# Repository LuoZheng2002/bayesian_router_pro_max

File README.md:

# On Windows:
At the root of the repository, double click on "installer.msi" to install and run the application.
# On Other Platform:
Download Rust and Tauri development toolchain, and at the repository root, run:

cargo tauri dev

for running the development version.

Or run

cargo tauri build

for building the released version.

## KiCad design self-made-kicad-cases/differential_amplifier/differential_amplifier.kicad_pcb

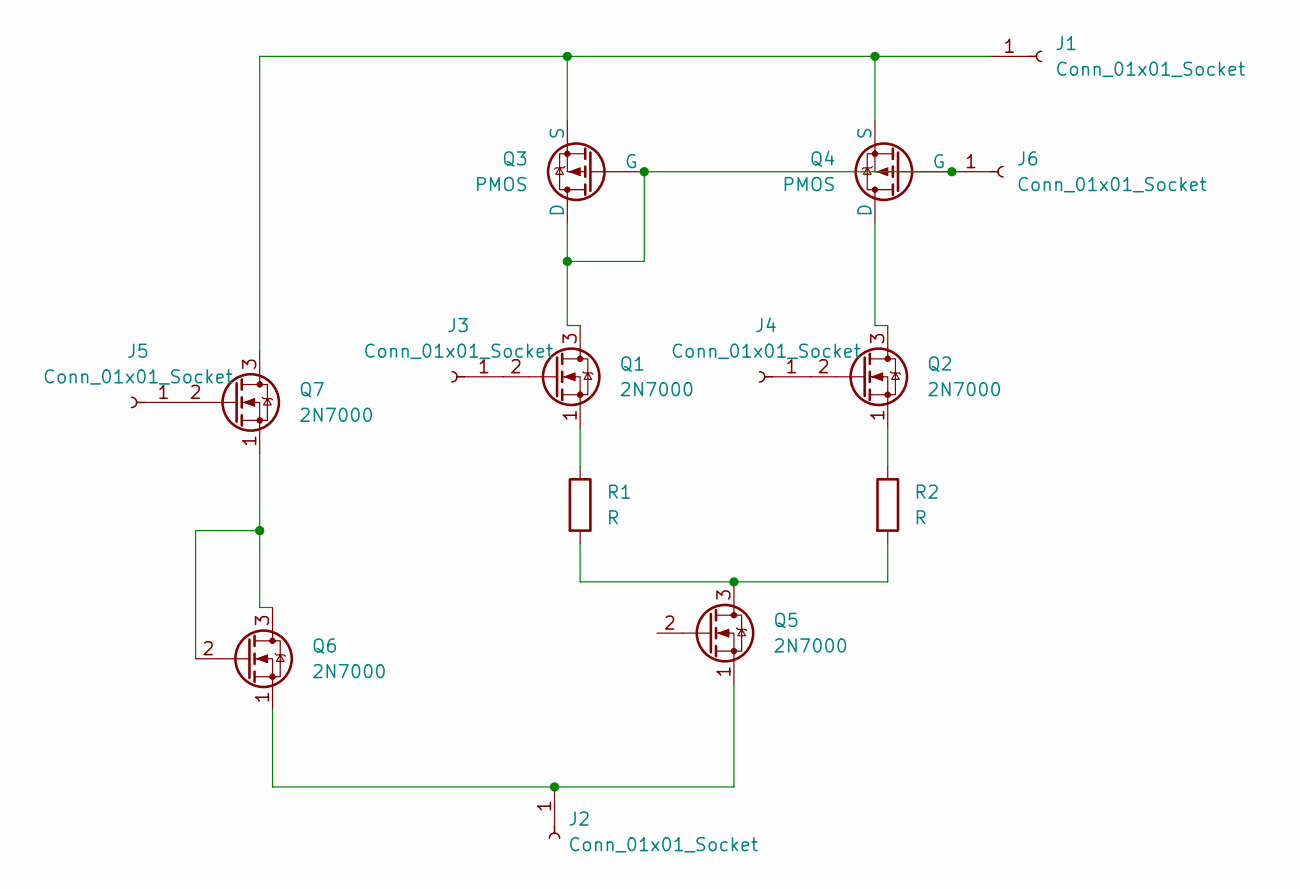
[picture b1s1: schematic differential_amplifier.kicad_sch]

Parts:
J1, J2, J3, J4, J5, J6: Conn_01x01_Socket; PinSocket_1x01_P2.54mm_Vertical
Q1, Q2, Q5, Q6, Q7: 2N7000; TO-92_Inline
Q3, Q4: PMOS; TO-92_Inline
R1, R2: R; R_Axial_DIN0207_L6.3mm_D2.5mm_P7.62mm_Horizontal

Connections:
unnamed: J1.1, Q3.3 (S), Q4.3 (S), Q7.3 (D)
unnamed: J2.1, Q5.1 (S), Q6.1 (S)
unnamed: J3.1, Q1.2 (G)
unnamed: J4.1, Q2.2 (G)
unnamed: J5.1, Q7.2 (G)
unnamed: J6.1, Q1.3 (D), Q3.1 (D), Q3.2 (G), Q4.2 (G)
unnamed: Q1.1 (S), R1.1
unnamed: Q2.3 (D), Q4.1 (D)
unnamed: Q2.1 (S), R2.1
unnamed: Q5.3 (D), R1.2, R2.2
unnamed: Q6.2 (G), Q6.3 (D), Q7.1 (S)

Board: 2 copper layers, 15 parts (0 on the bottom side), 11 nets, no tracks yet.

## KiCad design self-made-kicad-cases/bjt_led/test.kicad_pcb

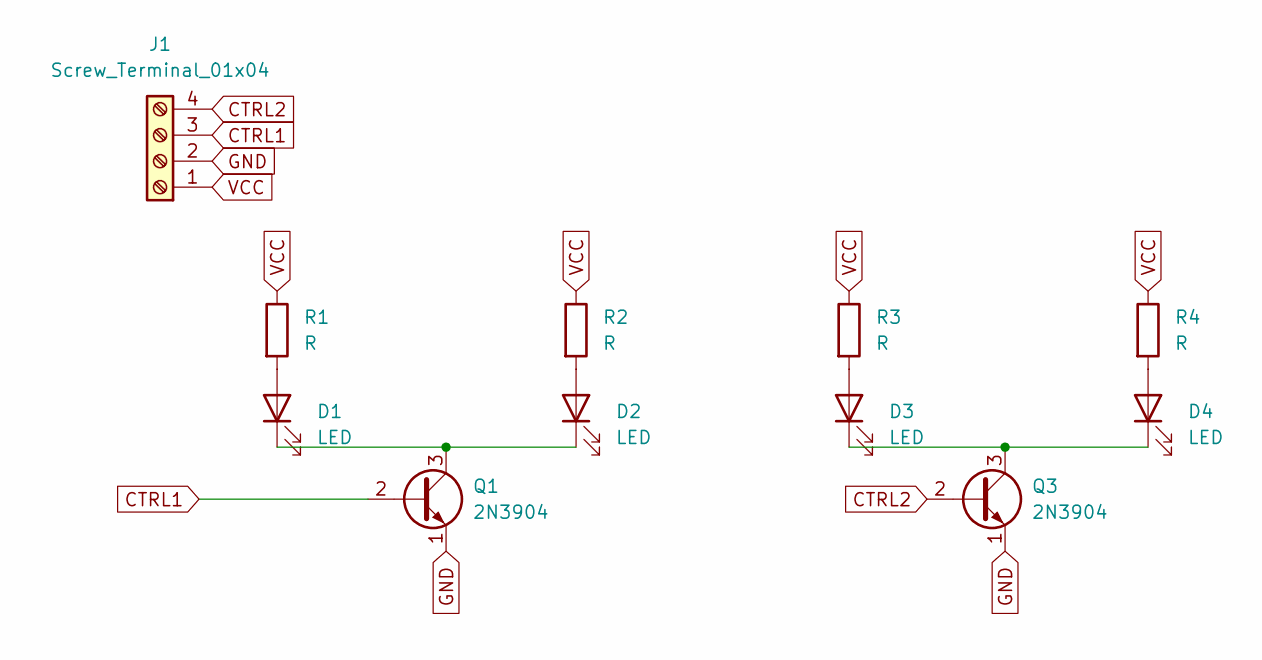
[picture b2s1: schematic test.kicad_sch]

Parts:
D1, D2, D3, D4: LED; LED_D5.0mm
J1: Screw_Terminal_01x04; TerminalBlock_Phoenix_MPT-0,5-4-2.54_1x04_P2.54mm_Horizontal
Q1, Q3: 2N3904; TO-92_Inline_Wide
R1, R2, R3, R4: R; R_Axial_DIN0207_L6.3mm_D2.5mm_P7.62mm_Horizontal

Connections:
CTRL1: J1.3, Q1.2 (B)
CTRL2: J1.4, Q3.2 (B)
GND: J1.2, Q1.1 (E), Q3.1 (E)
unnamed: D1.2 (A), R1.2
unnamed: D1.1 (K), D2.1 (K), Q1.3 (C)
unnamed: D2.2 (A), R2.2
unnamed: D3.2 (A), R3.2
unnamed: D3.1 (K), D4.1 (K), Q3.3 (C)
unnamed: D4.2 (A), R4.2
VCC: J1.1, R1.1, R2.1, R3.1, R4.1

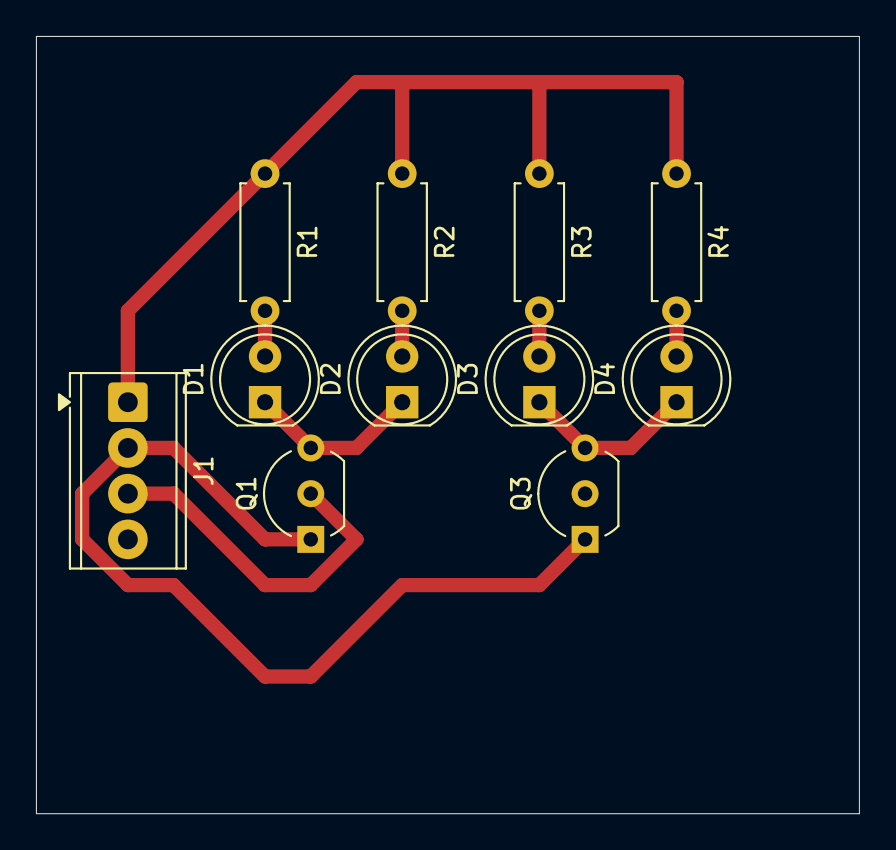
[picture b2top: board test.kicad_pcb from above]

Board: 2 copper layers, 45.7 x 43.2 mm, 11 parts (0 on the bottom side), 10 nets.

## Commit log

2025-07-28 checkpoint
2025-07-29 release
2025-07-29 fixed bugs and adjusted proba trace render
2025-07-30 bug fixes
2025-07-30 added kicad cases
2025-08-02 added demo functionality
2025-08-05 added installer and fixed minor bug
